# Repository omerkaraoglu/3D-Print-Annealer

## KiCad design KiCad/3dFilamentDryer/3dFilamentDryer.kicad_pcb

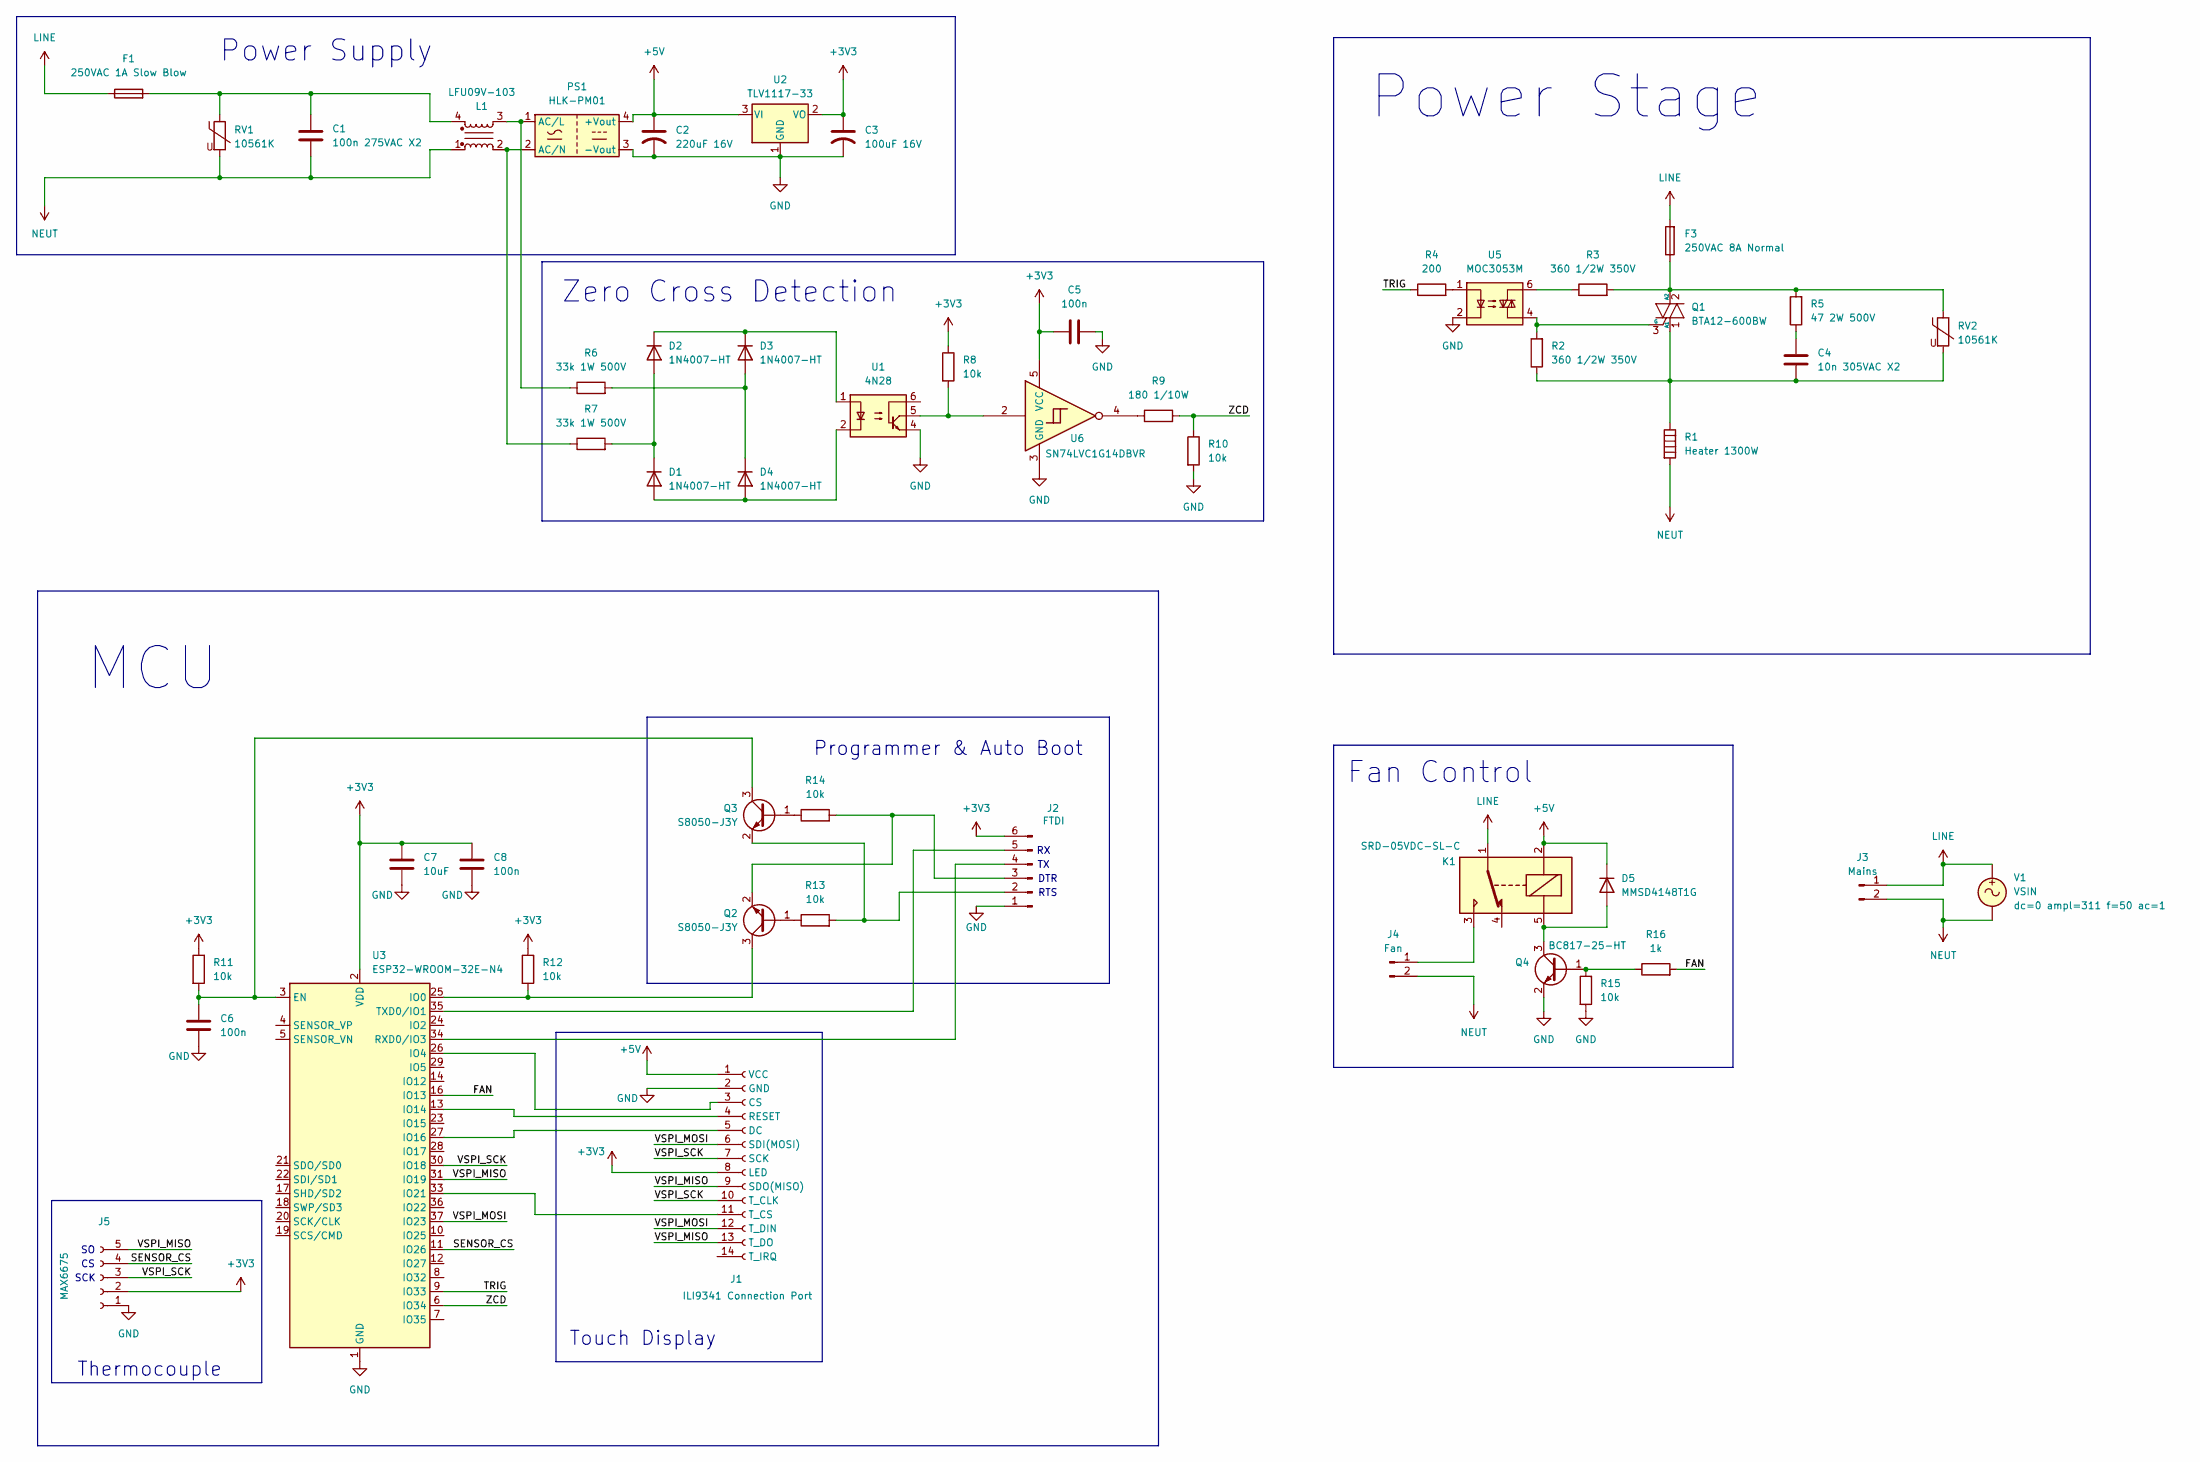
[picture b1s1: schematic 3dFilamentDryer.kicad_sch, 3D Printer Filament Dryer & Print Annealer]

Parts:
C1: 100n 275VAC X2; C_Rect_L18.0mm_W5.0mm_P15.00mm_FKS3_FKP3
C2: 220uF 16V; C_Radial_D6.3mm_H11.0mm_P2.50mm
C3: 100uF 16V; CP_Radial_Tantal_D5.0mm_P5.00mm
C4: 10n 305VAC X2; C_Rect_L13.0mm_W4.0mm_P10.00mm_FKS3_FKP3_MKS4
C5, C6, C8: 100n; C_0402_1005Metric
C7: 10uF; C_0603_1608Metric
D1, D2, D3, D4: 1N4007-HT; D_DO-41_SOD81_P10.16mm_Horizontal
D5: MMSD4148T1G; D_SOD-123
F1: 250VAC 1A Slow Blow; Fuseholder_Clip-5x20mm_Littelfuse_445-030_Inline_P20.50x5.2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
F3: 250VAC 8A Normal; Fuseholder_Clip-5x20mm_Littelfuse_445-030_Inline_P20.50x5.2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
J1: ILI9341 Connection Port; PinHeader_1x14_P2.54mm_Vertical
J2: FTDI; PinHeader_1x06_P2.54mm_Vertical
J3: Mains; SolderWire-1.5sqmm_1x02_P7.8mm_D1.7mm_OD3.9mm
J4: Fan; SolderWire-0.75sqmm_1x02_P7mm_D1.25mm_OD3.5mm
J5: MAX6675; PinHeader_1x05_P2.54mm_Vertical
K1: SRD-05VDC-SL-C; Relay_SPDT_SANYOU_SRD_Series_Form_C
L1: LFU09V-103
PS1: HLK-PM01; Converter_ACDC_Hi-Link_HLK-PMxx
Q1: BTA12-600BW; TO-220-3_Vertical
Q2, Q3: S8050-J3Y; SOT-23-3
Q4: BC817-25-HT; SOT-23
R1: Heater 1300W; SolderWire-1.5sqmm_1x02_P7.8mm_D1.7mm_OD3.9mm
R2, R3: 360 1/2W 350V; R_Axial_DIN0309_L9.0mm_D3.2mm_P12.70mm_Horizontal
R4: 200; R_0402_1005Metric
R5: 47 2W 500V; R_Axial_DIN0414_L11.9mm_D4.5mm_P15.24mm_Horizontal
R6, R7: 33k 1W 500V; R_Axial_DIN0414_L11.9mm_D4.5mm_P15.24mm_Horizontal
R8, R10, R11, R12, R13, R14, R15: 10k; R_0402_1005Metric
R9: 180 1/10W; R_0603_1608Metric
R16: 1k; R_0402_1005Metric
RV1, RV2: 10561K; RV_Disc_D12mm_W3.9mm_P7.5mm
U1: 4N28; DIP-6_W7.62mm
U2: TLV1117-33; SOT-223-3_TabPin2
U3: ESP32-WROOM-32E-N4; ESP32-WROOM-32E
U5: MOC3053M; DIP-6_W7.62mm
U6: SN74LVC1G14DBVR; SOT-23-5
V1: VSIN

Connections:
+3V3: C3.1, C5.1, C7.1, C8.2, J1.8 (LED), J2.6, J5.2, R8.1, R11.1, R12.1, U2.2 (VO), U3.2 (VDD), U6.5 (VCC)
+5V: C2.1, D5.1 (K), J1.1 (VCC), K1.2, PS1.4 (+Vout), U2.3 (VI)
/FAN: R16.2, U3.16 (IO13)
/SENSOR_CS: J5.4, U3.11 (IO26)
/TRIG: R4.1, U3.9 (IO33)
/VSPI_MISO: J1.9 (SDO(MISO)), J1.13 (T_DO), J5.5, U3.31 (IO19)
/VSPI_MOSI: J1.6 (SDI(MOSI)), J1.12 (T_DIN), U3.37 (IO23)
/VSPI_SCK: J1.7 (SCK), J1.10 (T_CLK), J5.3, U3.30 (IO18)
/ZCD: R9.2, R10.1, U3.6 (IO34)
GND: C2.2, C3.2, C5.2, C6.1, C7.2, C8.1, J1.2 (GND), J2.1, J5.1, PS1.3 (-Vout), Q4.2 (E), R10.2, R15.2, U1.4, U2.1 (GND), U3.1 (GND), U3.15 (GND), U3.38 (GND), U3.39 (GND), U5.2, U6.3 (GND)
LINE: F1.1, F3.2, J3.1, K1.1, V1.1
NEUT: C1.2, J3.2, J4.2, L1.1, R1.2, RV1.2, V1.2
unnamed: C1.1, F1.2, L1.4, RV1.1
unnamed: C4.1, R5.1
unnamed: D1.2 (A), D4.2 (A), U1.2
unnamed: D1.1 (K), D2.2 (A), R7.2
unnamed: D2.1 (K), D3.1 (K), U1.1
unnamed: D3.2 (A), D4.1 (K), R6.2
unnamed: D5.2 (A), K1.5, Q4.3 (C)
unnamed: J1.3 (CS), U3.26 (IO4)
unnamed: J1.5 (DC), U3.27 (IO16)
unnamed: J1.4 (RESET), U3.13 (IO14)
unnamed: J1.11 (T_CS), U3.33 (IO21)
unnamed: J2.2, Q3.2 (E), R13.2
unnamed: J2.3, Q2.2 (E), R14.2
unnamed: J2.4, U3.34 (RXD0/IO3)
unnamed: J2.5, U3.35 (TXD0/IO1)
unnamed: J4.1, K1.3
unnamed: L1.3, PS1.1 (AC/L), R6.1
unnamed: L1.2, PS1.2 (AC/N), R7.1
unnamed: C4.2, Q1.1 (A1), R1.1, R2.1, RV2.2
unnamed: F3.1, Q1.2 (A2), R3.2, R5.2, RV2.1
unnamed: Q1.3 (G), R2.2, U5.4
unnamed: Q2.1 (B), R13.1
unnamed: Q2.3 (C), R12.2, U3.25 (IO0)
unnamed: Q3.1 (B), R14.1
unnamed: C6.2, Q3.3 (C), R11.2, U3.3 (EN)
unnamed: Q4.1 (B), R15.1, R16.1
unnamed: R3.1, U5.6
unnamed: R4.2, U5.1
unnamed: R8.2, U1.5, U6.2
unnamed: R9.1, U6.4

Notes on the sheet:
Power Stage
Programmer & Auto Boot
SCK
RTS
Thermocouple
Power Supply
Touch Display
Fan Control
Zero Cross Detection
MCU
DTR

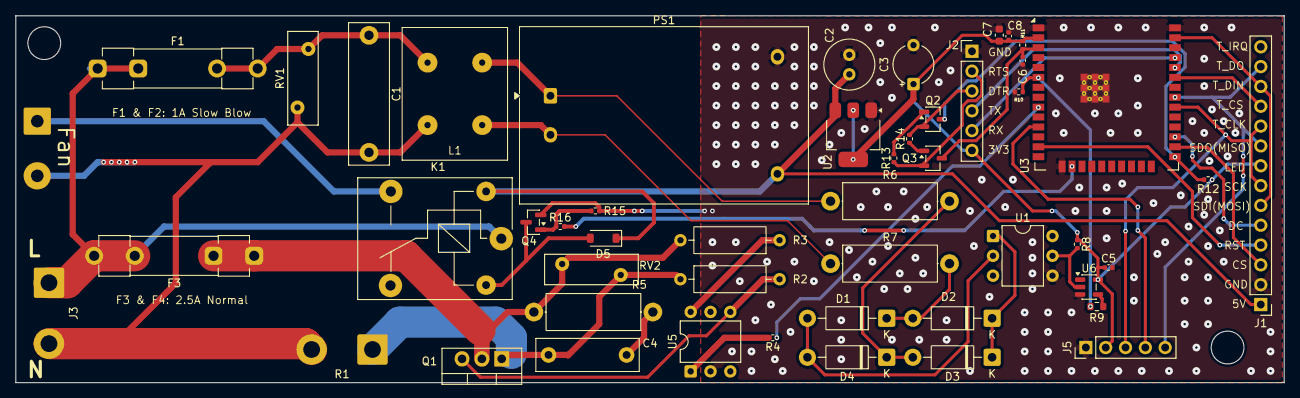
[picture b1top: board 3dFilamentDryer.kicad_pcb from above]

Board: 2 copper layers, 162.5 x 47.0 mm, 50 parts (1 on the bottom side), 42 nets.

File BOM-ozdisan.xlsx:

Reference | Qty | Value | Link
C1 | 1.0 | 100n 275VAC X2 | FARATRONIC C42P2104M6SC361 | Özdisan
C2 | 1.0 | 220uF 16V | KOSHIN PKLH-016V221ME110-T2.5 | Özdisan | LEHİM YAPILMAYACAK
C3 | 1.0 | 100uF 16V | KOSHIN PKRM-016V101MC110-T/A5.0 | Özdisan | Tedariği nasıl olacak?
C4 | 1.0 | 10n 305VAC X2 | FARATRONIC C42Q2103K40A405 | Özdisan | NOT
C5,C6,C8 | 3.0 | 100n | VIKING MCF02KTB250104 | Özdisan
C7 | 1.0 | 10uF | SAMSUNG CL10A106KP8NNNC | Özdisan
D1,D2,D3,D4 | 4.0 | 1N4007-HT | HOTTECH 1N4007-HT | Özdisan
F1,F2 | 2.0 | 250VAC 1A Slow Blow | REOMAX TBC1100A | Özdisan
F3,F4 | 2.0 | 250VAC 2.5A Normal | REOMAX 5GT2.5A | Özdisan
- | 8.0 | Fuse Holder Clip | REOMAX R3-5A | Özdisan
J1 | 1.0 | ILI9341 | 2.8inç SPI Dokunmatik TFT Ekran Modülü - 240x320 Piksel, ILI9341 Satın Al
J2 | 1.0 | FTDI | ~
J3 | 1.0 | Mains | ~
J4 | 1.0 | Fan | ~
J5 | 1.0 | MAX6675 | MAX6675 K-tip Isıl çift Termokupl Sensör
L1 | 1.0 | LFU09V-103 | CORE MASTER LFU09V-103 | Özdisan
PS1 | 1.0 | HLK-PM01 | HI-LINK HLK-PM01 | Özdisan
Q1 | 1.0 | BTA12-600BW | https://www.ozdisan.com/p/discrete-triyaklar-420/stm-bta12-6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
Q2,Q3 | 2.0 | S8050-J3Y | MDD S8050-J3Y | Özdisan
R1 | 1.0 | Heater 500W | ~
R2,R3 | 2.0 | 360 1/2W 350V | YAGEO MFR-50FTF52-360R | Özdisan
R4 | 1.0 | 200.0 | https://www.ozdisan.com/p/smt-smd-ve-cip-direncler-194/royal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
R5 | 1.0 | 47 2W 500V | ROYALOHM KNP02SJ0470A10 | Özdisan
R6,R7 | 2.0 | 33k 1W 500V | https://www.ozdisan.com/p/tht-dip-direncler-193/royalohm-cfr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
R8,R10,R11,R12,R13,R14 | 6.0 | 10k | ROYALOHM 0402WGJ0103TCE | Özdisan
R9 | 1.0 | 180 1/10W | ROYALOHM 0603SAJ0181T5E | Özdisan
RV1,RV2 | 2.0 | 10561K | THINKING TVR10561KFARY | Özdisan
U1 | 1.0 | 4N28 | ISOCOM 4N28 | Özdisan
U2 | 1.0 | TLV1117-33 | TEXAS TLV1117-33CDCYR | Özdisan
U3 | 1.0 | ESP32-WROOM-32 | ESP32-WROOM-32 4M 32Mbit Wi-Fi Bluetooth Modülü WiFİ Motorobit
U5 | 1.0 | MOC3053M | LITEON MOC3053M | Özdisan
U6 | 1.0 | SN74LVC1G14DBVR | TEXAS SN74AHC1G14DBVR | Özdisan
- | 1.0 | 1x14 Flat Ribbon Cable | CONNFLY DS1057-01-14A301R/76.5- | Özdisan | ILI9341 ile karttaki J1 arasında bu kablo olacak

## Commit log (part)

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2026-03-04 v1.2
2026-03-04 DEsign report updated
2026-04-13 PCB fix
2026-04-27 OTA without CA, factory reset & restore defaults settings added
2026-04-27 OTA with GitHub root CA
2026-04-27 OTA test
2026-04-27 v 2.1.1
2026-04-27 OTA test 2
2026-04-27 v2.1.1
2026-04-30 v2.1.2
2026-06-10 Firmware v2.1.2 Hardware Rev2
